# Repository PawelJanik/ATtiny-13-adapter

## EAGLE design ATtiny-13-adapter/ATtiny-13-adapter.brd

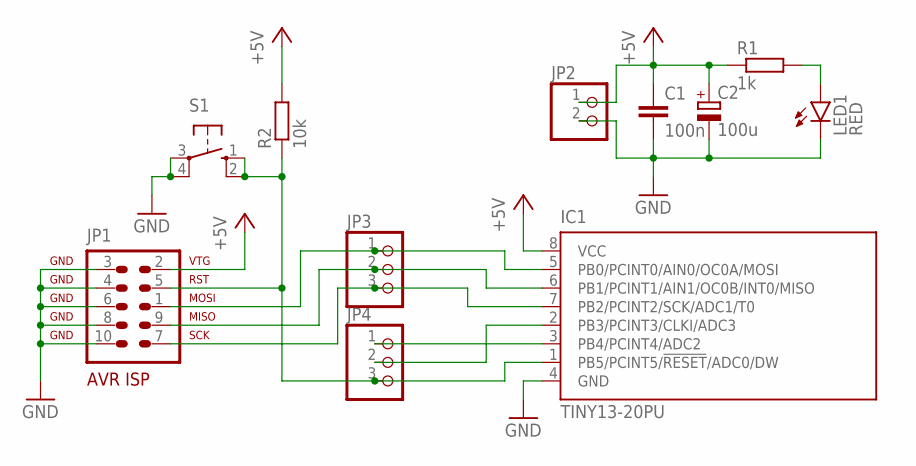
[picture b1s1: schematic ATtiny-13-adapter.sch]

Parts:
C1: 100n; C1206
C2: 100u; E2-5
IC1: TINY13-20PU; DIL08
JP1: AVR-ISP-10ML; ML10
JP2: PINHD-1X2; 1X02
JP3, JP4: PINHD-1X3; 1X03
LED1: RED; LED3MM
R1: 1k; R1206
R2: 10k; R1206
S1: 10-XX; B3F-10XX

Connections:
+5V: C1.1, C2.+, IC1.8 (VCC), JP1.2, JP2.1, R1.1, R2.2
GND: C1.2, C2.-, IC1.4 (GND), JP1.3, JP1.4, JP1.6, JP1.8, JP1.10, JP2.2, LED1.K (C), S1.3, S1.4 (P1)
unnamed: IC1.5 (PB0/PCINT0/AIN0/OC0A/MOSI), JP1.1, JP3.1
unnamed: IC1.6 (PB1/PCINT1/AIN1/OC0B/INT0/MISO), JP1.9, JP3.2
unnamed: LED1.A, R1.2
unnamed: IC1.7 (PB2/PCINT2/SCK/ADC1/T0), JP1.7, JP3.3
unnamed: IC1.2 (PB3/PCINT3/CLKI/ADC3), JP4.2
unnamed: IC1.3 (PB4/PCINT4/ADC2), JP4.1
unnamed: IC1.1 (PB5/PCINT5/!RESET!/ADC0/DW), JP1.5, JP4.3, R2.1, S1.1 (S), S1.2 (S1)

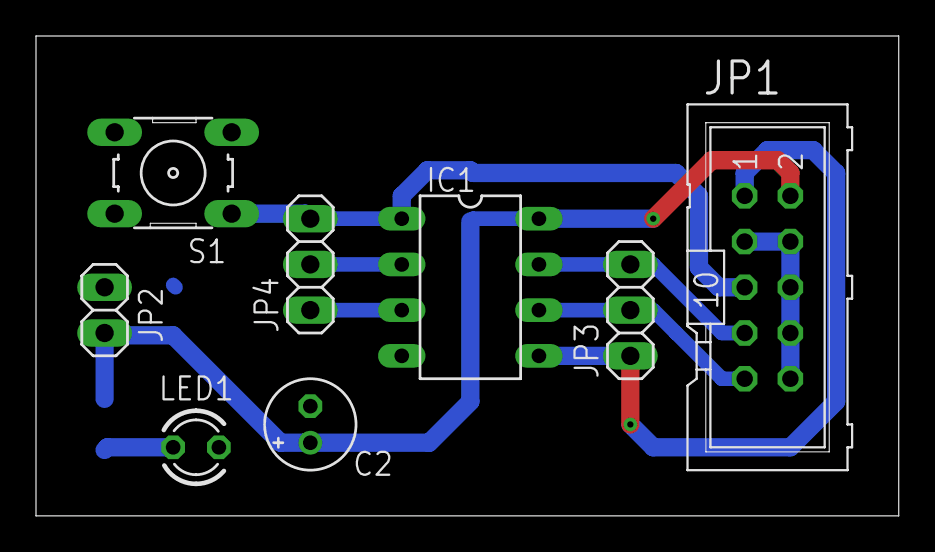
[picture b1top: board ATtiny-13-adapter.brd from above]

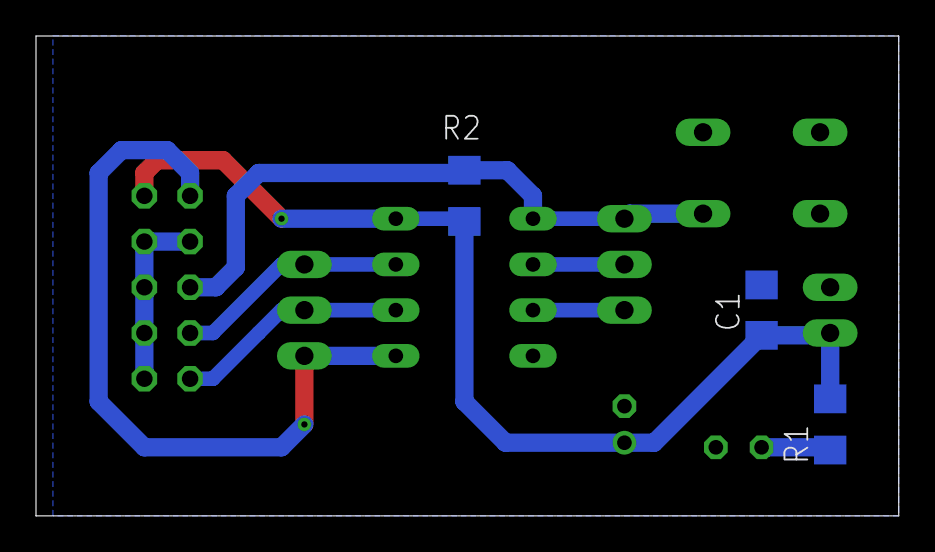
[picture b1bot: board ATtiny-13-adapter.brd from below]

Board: 2 copper layers, 47.9 x 26.7 mm, 11 parts (3 on the bottom side), 9 nets.
